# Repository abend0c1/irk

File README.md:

IRK! Infrared Remote USB Keyboard
=================================
Control your computer with an IR remote
---------------------------------------

IRK! is an open-hardware Infrared Remote Controlled USB keyboard, without keys, implemented using a PIC micro-controller and MikroC. It enables you to use your *learning* remote control to control any system that you can plug a USB keyboard into (Windows, Linux, Mac). Great for controlling a home theatre system such as MythTV, XBMC or Media Center. No drivers are required.

Note: Your IR remote *must* be able to *learn* infrared control signals. You *cannot* use a pre-programmed remote control with IRK!.

The original intention was to allow a user to control MythTV home theatre software using an infrared remote control. As it is seen by a PC as just another USB keyboard it can be used to control other PC functions as well.

What makes this unit different from the rest is that it can *teach* a learning remote control the IR code associated with a particular USB keystroke. As a result, there are *no* pre-programmed IR codes and IRK! does *not* have to support all the different types of infrared remotes on the market - it *teaches* the remote IRK!'s own infrared commands - which can be anything! Currently, IRK! uses Pulse Width Modulation (PWM) to encode/decode the infrared signals.

You can program -any- USB keyboard function (with or without Control, Alt, Shift and GUI modifiers) to a button on your infrared remote control and when you press that button IRK! will send the corresponding USB keystroke to the host computer.

You can program -any- USB Consumer Device control code too - for example, Play, Pause, Mute, Volume up, Volume down, and many others.

Features
--------
- Teaches your LEARNING remote control IR codes
- Lets you map IR codes to USB keystrokes - for example, Shift+Enter
- Sends the USB keystroke to your PC when you press a button on your infrared remote control
- Can send USB System Control codes (Power off, sleep, wake) to your PC
- Can can have one of 256 addresses - so you can have multiple IRK!'s
- Handles broadcasts - so multiple IRK!'s can respond to a single IR button
- Can remotely press the POWER and RESET buttons on your PC (if wired)
- Supports USB Consumer Device functions (e.g. Mute, Play, Pause, Stop, etc.)
- Has a programmable LCD backlight delay (and backlight ON/OFF commands)
- Requires NO drivers for Windows/Linux etc
- The Printed Circuit Board (PCB) comes in two flavours: 
  - Surface Mount Technology (SMT) and 
  - Through Hole Technology (THT)

Construction
------------
Go to the [Instructables](http://www.instructables.com/id/IRK-Infrared-Remote-Controlled-USB-Keyboard/) web site for detailed information on how to build your own unit.

Front Panel Buttons
-------------------

The front panel buttons comprise:

- UP - Press to increment the displayed function code. Press and hold to repeatedly increment the function code.
- DOWN - Press to decrement the displayed function code. Press and hold to repeatedly decrement the function code.
- OK - Press to accept an entry, or to cause the selected function to be executed.
- TEACH - Press to transmit a code representing the currently selected function to your IR remote control so that it can "learn" it.
- CTL - Press to toggle the keyboard "Ctrl" key. Press *and hold* to toggle the keyboard "GUI" key. The "GUI" key is a generic name for the "Windows" key on Microsoft keyboards, the "Apple" key on Apple keyboard, or the "Meta" or "Super" key on other keyboards. 
- ALT - Press to toggle the keyboard "Alt" key 
- SHIFT - Press to toggle the keyboard "Shift" key. Press *and hold* to select a different "usage page" (currently you can choose from Keyboard, Consumer Device, System Control, and local IRK! functions); then press UP/DOWN and OK to select the "usage page".

Front Panel Display 
-------------------

### Front Panel Display
The user is presented with an LCD 2 x 16 display that looks like:

<table style="border-collapse: collapse; width: 300px; text-align: left; background-color: #ccff00;">
  <tbody style="font-family: Courier New, courier, monospace; font-size: 20px; font-weight: bold; border: 10px solid #000000;">
    <tr><td style="padding-left:10px;width: 40px;">ux</td><td>line1</td></tr>
    <tr><td style="padding-left:10px;width: 40px;">yy</td><td>line2</td></tr>
  </tbody>
</table>

The codes, ux and yy, are hexadecimal values (that is, each digit can be from 0 to 9 and A to F).

-  u = The USB Usage Page index (i.e. used to assign meaning to the
      following x and yy codes). Press and hold the SHIFT button and
      then press the UP/DOWN buttons to cycle through the usage page
      indexes (0 to F and back to 0). At the moment, IRK! uses only
      the following usage page indexes:
    - 0 = Keyboard (A, B, C etc)
    - 1 = System Control (Power off, Sleep, Wake etc)
    - 2 = Consumer Devices (Mute, Vol+, Vol-, Play/Pause etc)
    - F = IRK! Local Functions (LCD backlight on/off etc)
- x = Either:
    - The key modifiers [Ctl, Alt, Shift, GUI] for Keyboard usage (see below), or else
    - The first nybble of xyy (the function to be performed) for all
          other usage pages.
- line1 = Text that describes the ux code
- yy = See below. Press and/or hold the UP and DOWN buttons to change
           the value of xyy.
- line2 = Text that describes the yy (or xyy) code.

The meanings id u, x and yy are as follows:

- When u = 0, xyy represents a Keyboard function:
    - 0x yy
         -    0 = Keyboard device
         -    x = Keyboard modifier (CTRL/ALT/SHIFT/GUI) flag bits (see below)
         -    yy = USB keyboard function code
    - 00 yy   Key yy pressed with no keyboard modifier keys
    - 01 yy   CTRL key pressed along with key yy
    - 02 yy   SHIFT key presed along with key yy
    - 04 yy   ALT key pressed along with key yy
    - 08 yy   GUI key pressed along with key yy
    
    Examples:
    - 00 05   b key pressed (05 is the code for "b")
    - 02 05   SHIFT+b key pressed (i.e. upper case B)
    - 06 05   ALT+SHIFT+b key pressed: 04(ALT) + 02(SHIFT) = 06(ALT+SHIFT)
    - 0C 05   GUI+SHIFT+b key pressed: 04(ALT) + 08(GUI)   = 0C(ALT+GUI)  

- When u = 1, xyy represents a System Control function:
    - 1x yy
         -    1 = System Control
         -    xyy = USB System Control function
    
    Examples:
    - 10 81   Power off
    - 10 82   Sleep
    - 10 83   Wake

- When u = 2, xyy represents a Consumer Device function:
    - 2x yy
         -   2 = Consumer Device
         -   xyy = USB Consumer Device function
     
    Examples:
    - 20 E2   Mute
    - 20 E9   Vol+
    - 20 EA   Vol-
    - 21 95   Internet Browser

- When u = F, xyy represents a local IRK! function (i.e. not USB):
    - Fx yy
         -   F = IRK! device
         -   xyy = Local IRK! device function
    - F0 00   Set Address ... the next LCD display will be:
        -    aa <-- Address
        -    00 Set Address
        -    You then press up/down to cycle the address (aa) then
             press OK to select it. The default address is AA.
    - F0 01   Power Switch
        - The two header pins marked PWR will become low impedance for about
          250 ms.  Note: this is not meant to switch large currents. The 4066
          quad analog switch can pass an absolute maximum of only +/- 25 mA.
    - F0 02   Reset Switch
        - The two header pins marked RST will become low impedance for about
          250 ms.
    - F0 03   Init USB
        - Causes the unit to re-register itself as a USB device. It is
          almost the equivalent of unplugging and replugging the device
          into a USB port.
    - F0 04   Back light off
        - Turns the LCD back light off
    - F0 05   Back light on
        - Turns the LCD back light off
    - F0 06   Set light delay  
        - Lets you set how many seconds you would like the LCD
          backlight to remain on after you have pressed a panel 
          button or issued a valid infrared command.
        - The next LCD display will be one of the following:
            -   xx <-- nnn secs (where nnn is xx in decimal)
            -   FF <-- ON       (keep back light always on)
            -   00 <-- OFF      (keep back light always off)
        -   You then press up/down to choose the delay value (xx) then
            press OK to select it.
    - F0 07   Debug on 
        - Displays debug information on the LCD when an IR code is received
    - F0 08   Debug off 
        - Returns the unit to Normal mode (displays no debug information on the LCD)
    - F0 0A   Auxiliary Switch
        - The two header pins marked AUX will become low impedance for about
          250 ms.
    - F0 11   Power Switch On
        - The two header pins marked PWR will become low impedance until a
          subsequent Power Switch Off command is received.
    - F0 12   Reset Switch On
        - The two header pins marked RST will become low impedance until a
          subsequent Power Switch Off command is received.
    - F0 1A   Auxiliary Switch On
        - The two header pins marked AUX will become low impedance until a
          subsequent Power Switch Off command is received.
    - F0 21   Power Switch Off
        - The two header pins marked PWR will become high impedance.
    - F0 22   Reset Switch Off
        - The two header pins marked RST will become high impedance.
    - F0 2A   Auxiliary Switch Off
        - The two header pins marked AUX will become high impedance.

- Other values (u = 3 to F) are currently reserved for future use.
            
Examples
--------            
1. The user wants to program the Enter key on the OK button of a
   learning remote control. The steps to follow are:
    - Plug IRK! into a host USB port
    - The default usage mode is Keyboard, which is displayed as
    "00 Keyboard" in the first line of the LCD, so just
    press and hold the UP button until the second line of the LCD
    shows "28 Enter".
    - Switch your learning remote control into "Learn" mode and
    select the remote's button to be programmed.
    - Press IRK!'s TEACH button. This will send an IR code that
    means "Enter" to your learning remote.
    - Repeat until the learning remote has learned that IR code.
    - Press the programmed button on the learning remote control.
    - Verify that IRK! has received the IR code (it will flash
    its LED when it has recognised a valid IR code). Verify 
    that the "Enter" USB Keyboard function has been performed
    at the host.

2. The user wants to program the "Mute" Consumer Devices function
   on the "Mute" button of a learning remote control. The default
   usage mode of IRK! is "Keyboard", so you need to switch IRK! into
   "Consumer Dev" mode first:
    - Press and hold IRK!'s SHIFT button until the second line of
    the LCD shows "^^ Select Usage".
    - Press IRK!'s UP button until "20 Consumer Dev" is displayed in
    the first line of the LCD.
    - Press IRK!'s OK button to enter "Consumer Dev" usage mode.
    - Press and hold IRK!'s UP button until "E2 Mute" is displayed
    on the second line of the LCD. If you overshoot then press the
    DOWN button repeatedly until you reach "E2 Mute".
    - Press OK to verify that the Mute function is accepted by the
    host.
    - Put your learning remote control into "Learn" mode and choose
    one of the remote's buttons to be programmed as "Mute".
    - Position your learning remote's IR receiver to within 5 cm of
    IRK!'s IR transmitter LED.
    - Press IRK!'s TEACH button. This will send an IR code that 
    means "Mute" to your learning remote.
    - Keep pressing TEACH until the learning remote has learned that
    IR code.
    - Press the programmed button on the learning remote control.
    - Verify that IRK! has received the IR code (it will flash
    its LED when it has recognised a valid IR code). Verify 
    that the "Mute" USB consumer device function has been performed
    at the host.

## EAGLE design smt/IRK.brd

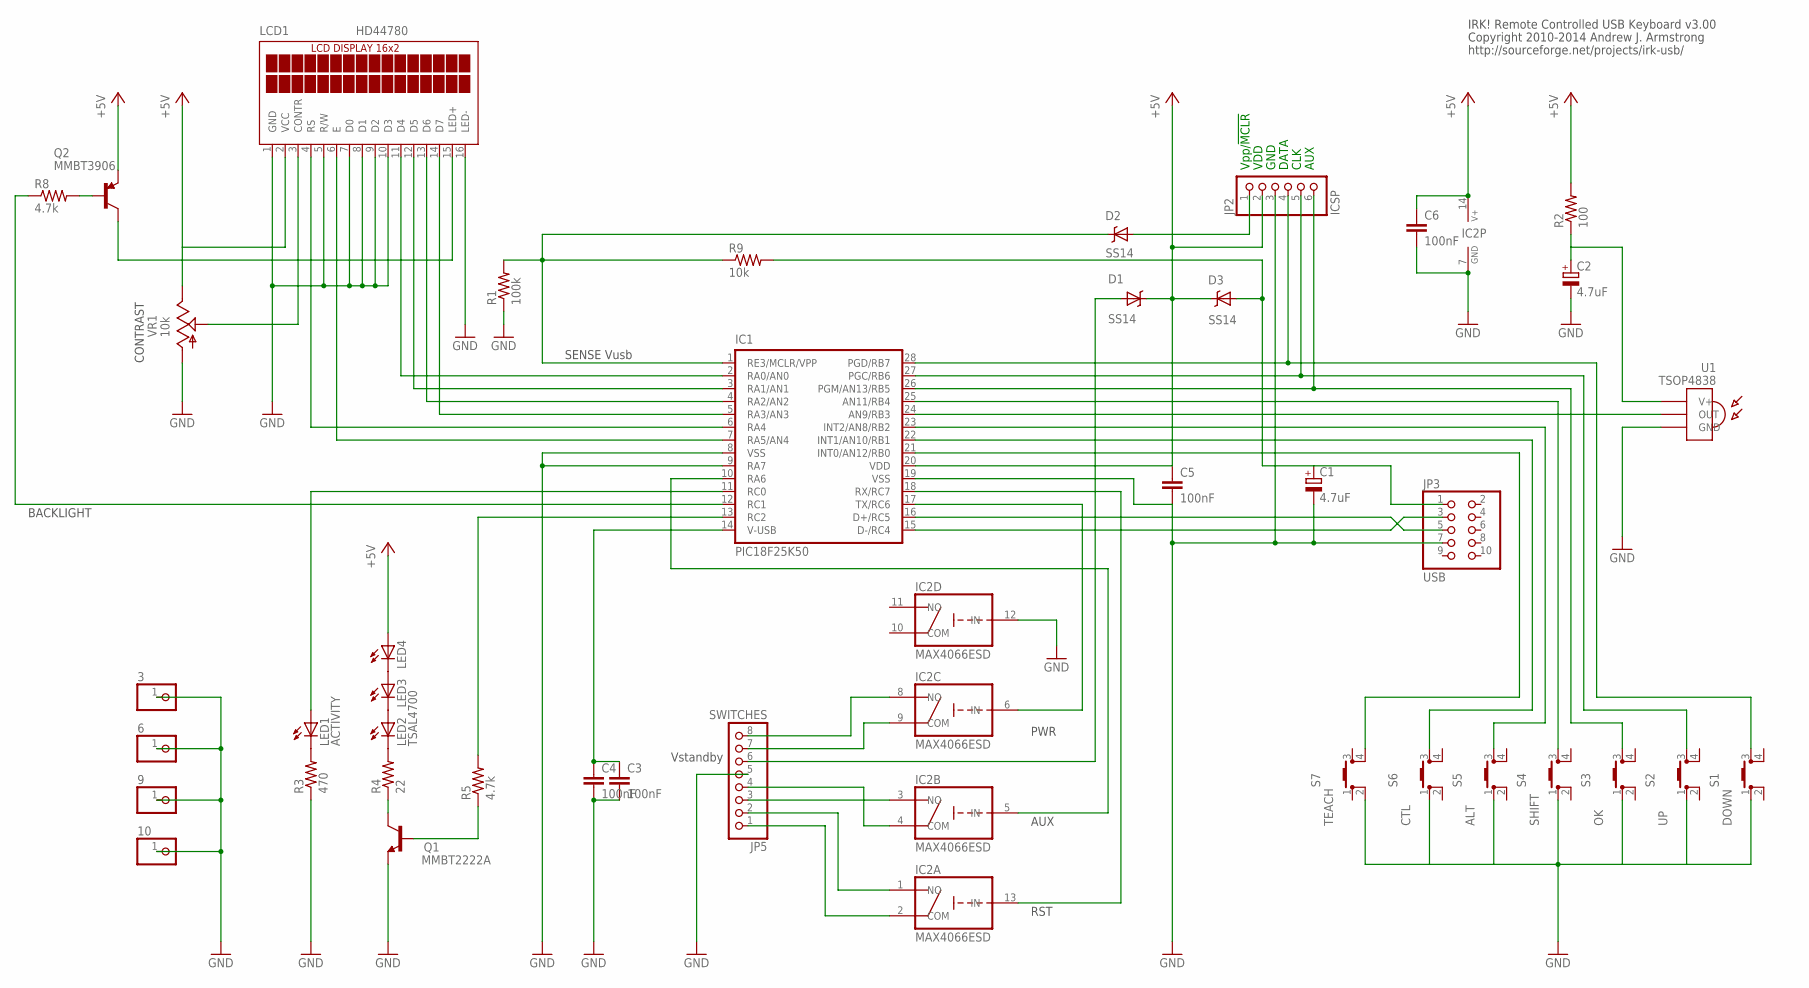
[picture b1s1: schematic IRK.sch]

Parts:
3, 6, 9, 10: 1X01
C1, C2: 4.7uF; SMC_A
C3, C4, C5, C6: 100nF; C0805
D1, D2, D3: SS14; SMA-DIODE
IC1: PIC18F25K50; SO28W
IC2: MAX4066ESD; SO14
JP2: ICSP; 1X06
JP3: USB; 2X05
JP5: SWITCHES; 1X08
LCD1: HD44780; LCD_16X2
LED1: ACTIVITY; LED5MM
LED2: TSAL4700; LED5MM
LED3, LED4: LED5MM
Q1: MMBT2222A; SOT23
Q2: MMBT3906; SOT23
R1: 100k; M1206
R2: 100; M1206
R3: 470; M1206
R4: 22; M1206
R5, R8: 4.7k; M1206
R9: 10k; M1206
S1: DOWN; PTH525-SM10
S2: UP; PTH525-SM10
S3: OK; PTH525-SM10
S4: SHIFT; PTH525-SM10
S5: ALT; PTH525-SM10
S6: CTL; PTH525-SM10
S7: TEACH; PTH525-SM10
U1: TSOP4838; TSOP18XX
VR1: 10k; 3303W

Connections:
+5V: C5.1, C6.1, D1.K, D3.K, IC1.20 (VDD), IC2.14 (V+), JP2.2, LCD1.2 (VCC), LED4.A, Q2.2 (E), R2.2, VR1.3 (E)
AUX: IC1.10 (RA6), IC2.5 (IN)
GND: 3.1, 6.1, 9.1, 10.1, C1.-, C2.-, C3.2, C4.2, C5.2, C6.2, IC1.8 (VSS), IC1.9 (RA7), IC1.19 (VSS), IC2.7 (GND), IC2.12 (IN), JP2.3, JP3.7, JP5.5, LCD1.1 (GND), LCD1.5 (R/W), LCD1.7 (D0), LCD1.8 (D1), LCD1.9 (D2), LCD1.10 (D3), LCD1.16 (LED-), Q1.2 (E), R1.1, R3.1, S1.1, S2.1, S3.1, S4.1, S5.1, S6.1, S7.2, U1.GND, VR1.1 (A)
unnamed: IC1.2 (RA0/AN0), LCD1.11 (D4)
unnamed: IC1.3 (RA1/AN1), LCD1.12 (D5)
unnamed: IC1.4 (RA2/AN2), LCD1.13 (D6)
unnamed: IC1.5 (RA3/AN3), LCD1.14 (D7)
unnamed: IC1.6 (RA4), LCD1.4 (RS)
unnamed: IC1.7 (RA5/AN4), LCD1.6 (E)
unnamed: LCD1.3 (CONTR), VR1.2 (S)
unnamed: D2.K, IC1.1 (RE3/MCLR/VPP), R1.2, R9.1
unnamed: IC1.24 (AN9/RB3), U1.OUT
unnamed: IC2.2 (COM), JP5.1
unnamed: IC1.28 (PGD/RB7), JP2.4, S1.3
unnamed: IC1.27 (PGC/RB6), JP2.5, S2.3
unnamed: IC1.26 (PGM/AN13/RB5), JP2.6, S3.3
unnamed: IC1.25 (AN11/RB4), S4.3
unnamed: IC1.23 (INT2/AN8/RB2), S5.3
unnamed: IC1.22 (INT1/AN10/RB1), S6.3
unnamed: IC1.21 (INT0/AN12/RB0), S7.4
unnamed: C3.1, C4.1, IC1.14 (V-USB)
unnamed: LED1.K (C), R3.2
unnamed: C1.+, D3.A, JP3.1, R9.2
unnamed: IC2.1 (NO), JP5.2
unnamed: IC1.16 (D+/RC5), JP3.5
unnamed: IC1.15 (D-/RC4), JP3.3
unnamed: LED2.K (C), R4.2
unnamed: LED2.A, LED3.K (C)
unnamed: LED3.A, LED4.K (C)
unnamed: IC1.13 (RC2), R5.2
unnamed: Q1.1 (B), R5.1
unnamed: Q1.3 (C), R4.1
unnamed: LCD1.15 (LED+), Q2.3 (C)
unnamed: IC2.4 (COM), JP5.4
unnamed: IC1.12 (RC1), R8.1
unnamed: IC2.3 (NO), JP5.3
unnamed: Q2.1 (B), R8.2
unnamed: IC2.9 (COM), JP5.7
unnamed: IC2.8 (NO), JP5.8
unnamed: D2.A, JP2.1
unnamed: IC1.11 (RC0), LED1.A
unnamed: C2.+, R2.1, U1.VCC (V+)
PWR: IC1.17 (TX/RC6), IC2.6 (IN)
RST: IC1.18 (RX/RC7), IC2.13 (IN)
VSB: D1.A, JP5.6

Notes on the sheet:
RST
PWR
CONTRAST
Copyright 2010-2014 Andrew J. Armstrong
http://sourceforge.net/projects/irk-usb/
IRK! Remote Controlled USB Keyboard v3.00
BACKLIGHT
SENSE Vusb
Vpp/!MCLR
VDD
GND
DATA
CLK
AUX
Vstandby

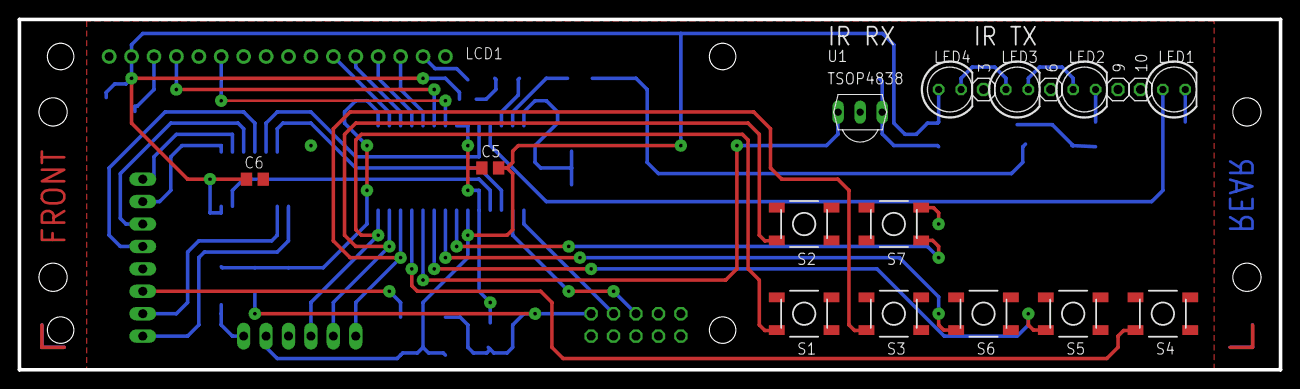
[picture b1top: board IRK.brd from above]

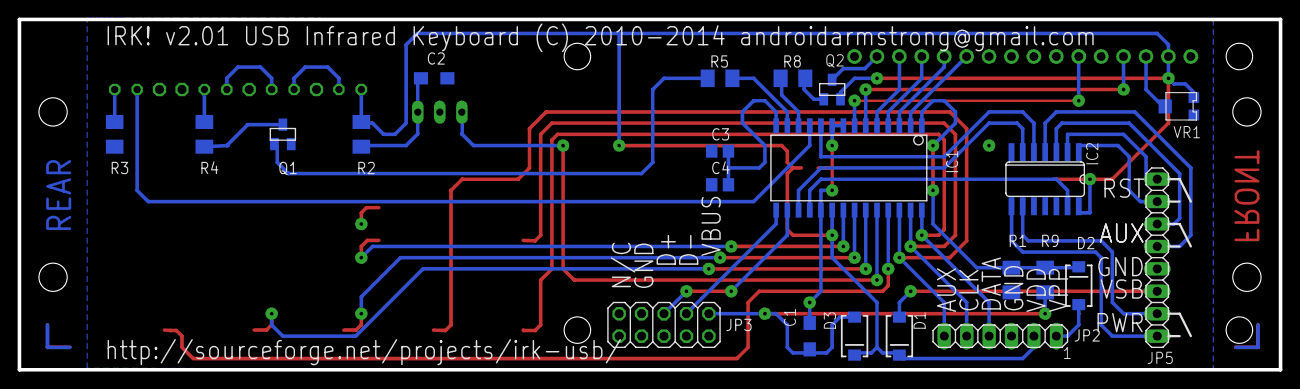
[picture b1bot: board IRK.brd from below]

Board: 2 copper layers, 142.9 x 39.7 mm, 41 parts (22 on the bottom side), 45 nets.

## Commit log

2012-08-14 Initial git commit - version 2.04
2012-08-14 Added change log
2012-10-09 Fixed the pulse width check introduced in 2.04
2012-10-14 Debug mark 1
2012-10-20 Increased IR pulse width error margin and added debug mode
2012-10-20 Updated change history for 2.06
2012-10-20 Updated change.log for 2.06
2012-10-25 Added extra Consumer Device function descriptions
2012-10-27 Updated change log for 2.07
2012-12-11 Huge reduction in RAM usage
2012-12-12 Reserve RAM bank 4 for USB
2012-12-12 Fixed bug when holding SHIFT during menu navigation
2012-12-13 Long press CTL key toggles GUI key modifier
2012-12-17 Updated pin usage diagram
2013-04-14 Recompile for MikroC 6.0
2013-11-10 Added a new SMD double-sided board and schematic
2013-11-16 Reworked SMD board layout
2013-12-05 Added .gitattributes text=auto
2013-12-05 Reworked project structure to accommodate SMD and THT versions.
    The orginal Through Hole Technology (THT) version is now stored
    in the tht/ directory and the new Surface Mount Technology (SMT)
    version is stored in the smt/ directory.
2013-12-05 Cleaned up IRK.lbr (Eagle CAD device library)
    Also, added a footprint for a very cheap micro-tactile switch
    from Leye Electronics (China) - available on eBay. If you want
    to use it you will have to redesign the PCB slightly as it is
    a 6mm x 6mm SMT switch - larger than the C&K switch in the SMT
    version.
2013-12-05 Changed symbol for push button switches
2013-12-07 Added README.md
2013-12-07 Added IRK Function Codes spreadsheet
2013-12-07 Added Auxiliary switch logic
2013-12-10 Made cosmetic changes.
    1. Used the HID Report Descriptor Decoder (http://sourceforge.net/projects/hidrdd/)
    to document the report descriptor meaning.
    2. Changed the trimpot in IRK.lbr so that it has a tRestrict under it (this
    prevents copper traces being routed under the metal part of the trimpot).
    3. Improved the routing of the track for the 100nF capacitor under the PIC18F25K50
    chip.
2013-12-10 Updated the CAM job to print component values on the top and bottom silk.
2013-12-10 Updated the TSOP4838 IR receiver footprint to have the Name and Value on the tNames and tValues layers respectively. Was on tPlace in error.
2013-12-11 Replaced old 2550 device with P18F25K50 in IRK.lbr
2013-12-11 Added smt/IRK.hex
2013-12-11 Ran the smt/IRK.cam job to re-create the Gerber files
    These files (*.g*) can be sent to a PCB manufacturer. This time the
    component values will be printed on the silk layers. The batch I got
    back from Itead only had the component names (my bad).
2013-12-11 Updated change log
2013-12-11 Added a script to zip up the gerber files. You specify the version to suffix the zip file name
2013-12-16 Spaced the holes for the IR TX and Activity LEDs at 0.1 inch intervals.
    Now (if you want) you can solder a 12x1 pin socket header and plug
    your IR TX and Activity LEDs into it rather than soldering them
    directly to the board. Long term reliability might be an issue
    as the leads oxidise though. The interspersed pin sockets appear on
    the schematic as grounded 1x1 header pins.
    The IR RX LED has remained slightly offset from the others, because it
2013-12-21 Reworked to run at 48 MHz (instead of 24 MHz).
    - Fixed description of what the front panel buttons do in README.md
    - Changed some configuration fuses (CONFIGxx) for PIC18F25K50
    - Reworked the timer value calculations so that the MCU clock frequency
    can be reverted to 24 MHz more easily.
    - Minor changes to the Eagle PCB layout, library and schematic.
    Note: Infrared capture is still not working at the moment, but things
2013-12-28 Tidied up the source code a bit.
2013-12-28 Tidied up the source code a bit.
    - Infrared capture works (it worked all along, it's just that I
    forgot to set the IRK device address to AA - the deafault is FF).
2013-12-28 Updated version to 3.02
2013-12-29 Added extra local IRK! functions to turn on and off the 4066 analog switches.
    The existing local functions merely asserted the selected analog
    switch (PWR, RST and AUX) for 250 ms. The new functions allow you
    to assert each analog switch until they are released by a
    subsequent OFF command.
2013-12-29 Renumbered the analog switch local IRK! function codes
2013-12-30 Updated the LCD package to have 3 mm mounting holes.
    The original ones were 2.5 mm but didn't match reality.
    So I had to drill out the mounting holes to 3 mm (or else
    find 2.5 mm bolts which are quite hard to find). M3 bolts
    are much more commonly available. Had to reroute one of the
    PCB traces to avoid a hole as a result.
2014-02-11 Updated IRK Local Function documentation
2014-08-31 Corrected documentation in USBdsc.c regarding EP_IN_INTERVAL. Added FPC connector to Eagle smt part library.
2014-12-05 Used Hi() and Lo() functions. Introduced ASSIGN macro to assign names to each LCD pin.

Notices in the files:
smt/IRK.brd:
IRK! v2.01 USB Infrared Keyboard (C) 2010-2014 androidarmstrong@gmail.com
parts and their libraries:
SparkFun-Electromechanical: Licensing: CC v3.0 Share-Alike You are welcome to use this library for commercial purposes.
